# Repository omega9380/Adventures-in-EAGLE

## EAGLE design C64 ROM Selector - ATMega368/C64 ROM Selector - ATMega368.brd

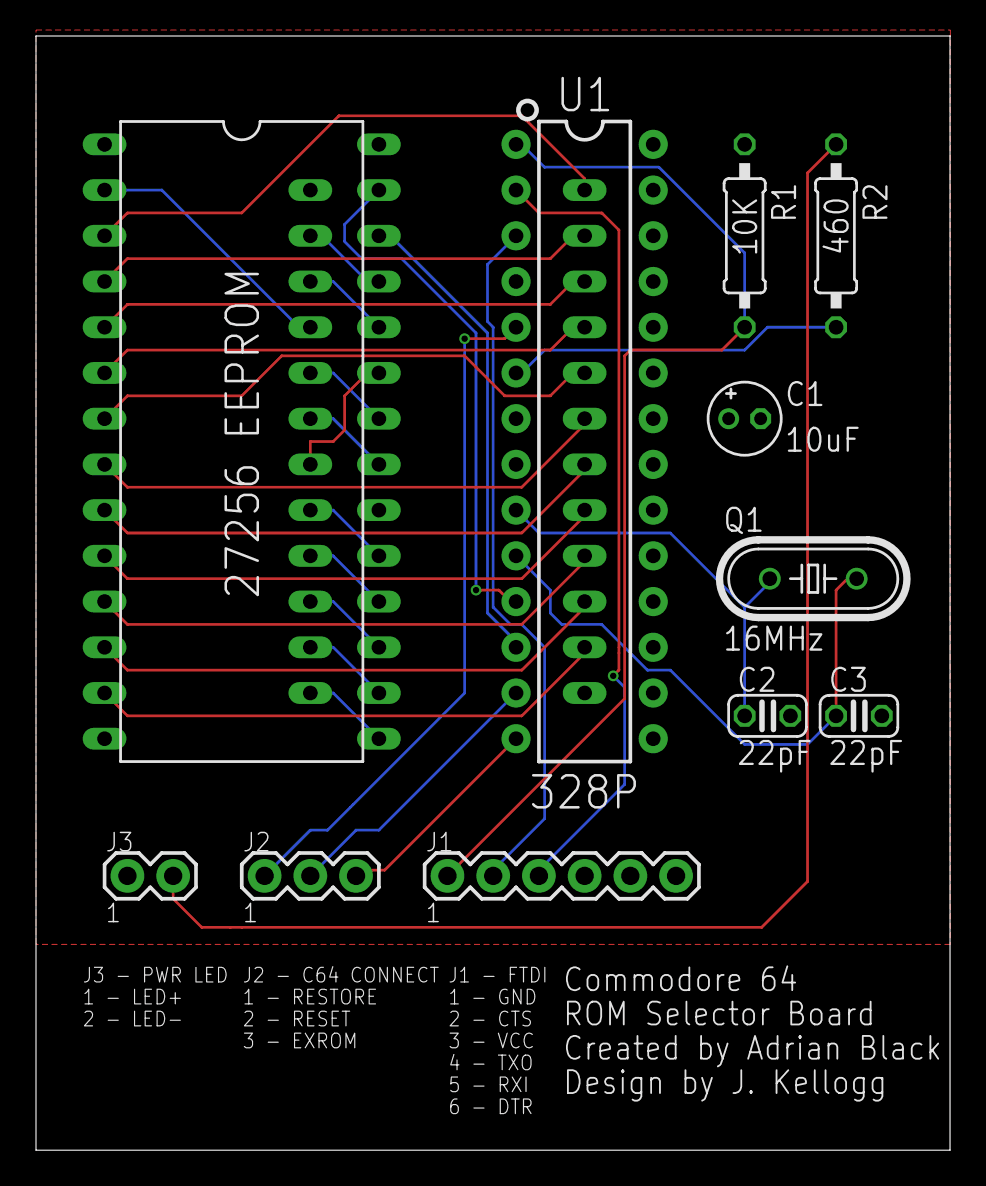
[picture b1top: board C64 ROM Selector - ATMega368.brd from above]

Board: 2 copper layers, 50.8 x 61.9 mm, 12 parts (1 on the bottom side), 36 nets.

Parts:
C1: 10uF; E1,8-4
C2, C3: 22pF; C025-024X044
IC1: C64 ROM SOCKET; DIL24
IC2: 27256 EEPROM; DIL28
J1: FTDI Basic; 1X06
J2: C64; 1X03
J3: PLED; 1X02
Q1: 16MHz; HC49/S
R1: 10K; 0207/10
R2: 460; 0207/10
U1: 328P; DIP28

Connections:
!CE: IC1.20, IC2.22
!RESET: J1.1, R1.2, U1.1
A0: IC1.8, IC2.10
A1: IC1.7, IC2.9
A2: IC1.6, IC2.8
A3: IC1.5, IC2.7
A4: IC1.4, IC2.6
A5: IC1.3, IC2.5
A6: IC1.2, IC2.4
A7: IC1.1, IC2.3
A8: IC1.23, IC2.25
A9: IC1.22, IC2.24
A10: IC1.19, IC2.21
A11: IC1.18, IC2.23
A12: IC1.21, IC2.2
A13: IC2.26, U1.12
A14: IC2.27, U1.11
D0: IC1.9, IC2.11
D1: IC1.10, IC2.12
D2: IC1.11, IC2.13
D3: IC1.13, IC2.15
D4: IC1.14, IC2.16
D5: IC1.15, IC2.17
D6: IC1.16, IC2.18
D7: IC1.17, IC2.19
GND: C1.-, C2.2, C3.2, IC1.12, IC2.14, IC2.20, J1.5, J1.6, J3.1, U1.8, U1.22
PIN3: J2.1, U1.5
PIN4: R2.2, U1.6
PIN7: J2.2, U1.13
PIN8: J2.3, U1.14
PIN9: C2.1, Q1.1, U1.9
PIN10: C3.1, Q1.2, U1.10
PLED+: J3.2, R2.1
RXI: J1.3, U1.2
TXO: J1.2, U1.3
VCC: C1.+, IC1.24, IC2.1, IC2.28, J1.4, R1.1, U1.7, U1.20

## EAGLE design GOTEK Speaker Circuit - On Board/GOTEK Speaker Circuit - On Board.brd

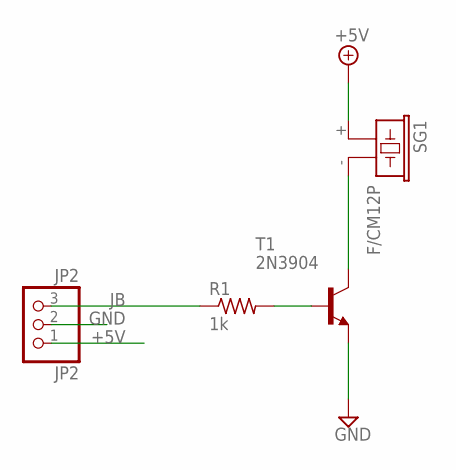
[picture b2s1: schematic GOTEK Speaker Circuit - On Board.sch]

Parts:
JP2: JP2; 1X03
R1: 1k; 0204/7
SG1: F/CM12P
T1: 2N3904; TO92

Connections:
+5V: JP2.1, SG1.+ (1)
GND: JP2.2, T1.3 (E)
JB: JP2.3, R1.1
unnamed: R1.2, T1.2 (B)
SPK-: SG1.- (2), T1.1 (C)

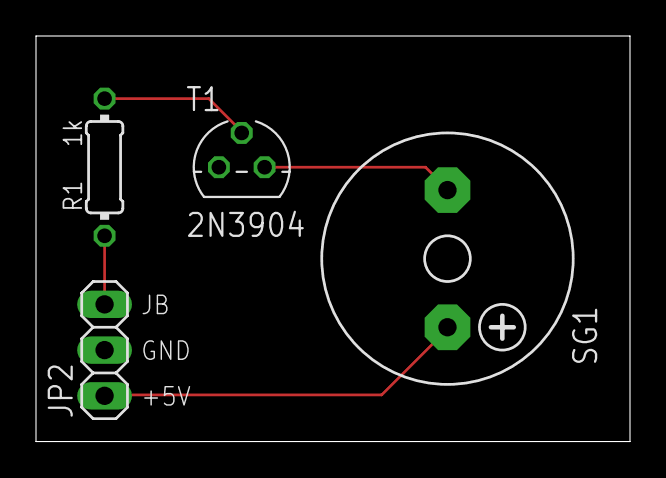
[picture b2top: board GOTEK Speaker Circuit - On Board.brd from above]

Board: 2 copper layers, 33.0 x 22.5 mm, 4 parts (0 on the bottom side), 5 nets.

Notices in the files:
parts and their libraries:
SparkFun-Connectors: Licensing: Creative Commons ShareAlike 4.0 International - https://creativecommons.org/licenses/by-sa/4.0
